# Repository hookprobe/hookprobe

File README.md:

<h1 align="center">One Node's Detection → Everyone's Protection</h1>

<p align="center">
  <strong>One security operating system. One shared evidence model. Multiple operator workspaces.</strong>
</p>

<p align="center">
  Current release: <a href="docs/releases/v0.0-26.md"><strong>HookProbe OS v0.0-26 "Zamolxis"</strong></a> (pre-release)
</p>

<p align="center">

</p>

<p align="center">
  <a href="#what-hookprobe-can-do">What it can do</a> ·
  <a href="#system-architecture">Architecture</a> ·
  <a href="#try-hookprobe">Try HookProbe</a> ·
  <a href="#hardware-roadmap-the-hookprobe-board">Hardware roadmap</a> ·
  <a href="CONTRIBUTING.md">Contribute</a>
</p>

---

## What HookProbe can do

HookProbe OS is designed to put practical security within reach: a local-first security operating
system that can observe a network, identify suspicious activity, connect detections to evidence,
and give an operator one place to understand and control what happens next.

**The operating system is HookProbe OS. SOC is its default workspace. Hardware only unlocks capabilities.**

### Manage it one way, from any client

Every management client talks to the device through **one management interface** (the management
ABI), and one component inside the kernel, **`cfgd`**, is the only thing that writes configuration.

```text
   hsh (native shell, EL0)     Mission Control (web UI)     AI copilot (tools)
              └──────────────────────┼──────────────────────┘
                          management ABI
                                     │
                     cfgd — the single configuration writer
            authenticate · authorize · validate · stage · trial · commit / revert
```

- **`hsh`** is HookProbe's own management shell, built into the kernel. It is not Bash, BusyBox or a
  Linux shell. It runs as an isolated user-mode component, sees the same numbers Mission Control
  does, and cannot reach kernel internals. Its read commands pass on CM5
  ([batch 59–63](docs/design/metal-evidence/20261111-batch59-63.md)). Production access was decided on
  2026-11-12: a console in Mission Control over the owner's HTTPS session; every command that changes
  something needs a request signed off-device with the owner's key, so the console itself carries no
  authority. That signed path is QEMU-tested only (metal pending); no serial-console access is built.
  See the [`hsh` design](docs/design/hsh-native-management-shell.md) and the
  [signed request format](docs/design/mgmt-envelope-api.md).
- **Mission Control** is the web UI, served by the device itself. It is a client of the same
  interface, with nothing UI-specific on the device.
- **Configuration is signed, not trusted.** The owner holds a signing key (in the browser, with an
  encrypted backup) and enrolls it as the device's owner key; after that the device accepts only
  configuration signed with it. Internet, Wi-Fi and firewall settings travel as one signed bundle,
  bound to the device. A bundle starts as a **trial**: the device keeps it once the internet works,
  or goes back to the last good settings by itself (proven on CM5 after a reboot,
  [batch 59–63](docs/design/metal-evidence/20261111-batch59-63.md)). Changes to how you reach the
  device must be confirmed by the owner, with a request signed by the owner's key.
- Built on main 2026-11-12, **QEMU-tested only, not yet run on CM5**: stored configuration (including
  the Wi-Fi and PPPoE passwords) encrypted at rest with a device-bound key, and firewall, internet and
  Wi-Fi changes applied live, without a reboot, with the same trial and automatic revert
  ([design and status](docs/design/heqk-sealed-config-live-apply.md)).
- Still to come: passkey signing.

Details: [ADR 0058](docs/adr/0058-owner-signed-runtime-config.md) (owner-signed configuration),
[ADR 0059](docs/adr/0059-secure-configuration-management.md) (secure configuration management) and
the [Mission Control UI requirements](docs/design/mission-control-ui-requirements.md).

### Protect locally

Inspect and respond at the device, without making cloud connectivity, an account, or an AI service a
precondition for local protection. Detection is designed to be observable by default; enforcement
is a separate, policy-controlled decision that protects legitimate traffic and management access.

### Turn signals into an understandable story

Bring supported network and device signals into a shared evidence model. Link a detection to its
flows, affected assets, related events, and response so an operator can move from “something
happened” to “why it matters” without jumping between disconnected tools.

### Operate one system through many workspaces

Mission Control is the operator's home. Observe, Detect, Investigate, Protect, Network, Intelligence,
and other workspaces are views over shared system state—not separate products with separate data.
The same evidence can support a responder's investigation and an operator's broader view.

### Make security decisions reviewable

State an outcome instead of hand-editing a pile of device settings. AEGIS is designed to reconcile
authorized desired state deterministically; an optional AI planner can help turn intent into an
explainable plan. The kernel—not an AI model—remains responsible for enforcing authorized policy.

### Grow from one device to a fleet

Start standalone, including in disconnected environments. Add a cloud-linked or self-hosted control
plane when fleet coordination is useful. The longer-term vision is opt-in sharing of validated,
privacy-preserving threat knowledge, so one node's detection can help protect others; a live global
threat-sharing mesh is not a prerequisite for the product.

## System architecture

HookProbe connects local signals to local decisions and operator-visible evidence. Hardware
capabilities shape what a device can do; they do not turn it into a different product.

<p align="center"><em>One local system, one evidence model, many views. Fleet coordination is additive.</em></p>

| Part of the system | Responsibility |
|---|---|
| **heqk and platform capabilities** | The intended common OS substrate. A platform contributes its hardware port and the capabilities it can safely provide. |
| **Local packet and policy path** | Examines supported traffic and applies an explicit, locally enforceable verdict. It does not depend on a browser, cloud, or model response. |
| **Senzorium** | Observation and telemetry: bring supported signals into a useful, normalized form. |
| **NAPSE, QSecBit, and HYDRA** | Network threat detection, security-posture signals, and threat-intelligence enrichment. |
| **Evidence graph** | Connects assets, events, detections, incidents, and responses so each workspace can follow the same facts. |
| **AEGIS** | Reconciles authorized intent into system state; optional AI assists planning but does not enforce it. |
| **cfgd and the management ABI** | The single writer of device configuration: checks who asks and what is signed, stages a change as a trial, commits it or reverts it. Every management client goes through it. |
| **hsh** | HookProbe's own management shell inside the kernel: a small, deterministic command line over the same management ABI. |
| **Mission Control** | The on-device web experience, with workspaces for understanding and managing the system; a client of the same management ABI. |
| **Optional control plane** | Adds fleet enrollment and coordination without becoming a requirement for local operation. |

These are architectural responsibilities, not a promise that every named service is already a
separate process on every device. The [high-level design](docs/design/hookprobe-high-level-design.md)
explains the product boundaries; the [heqk low-level design](docs/design/heqk-low-level-design.md)
covers the kernel, hardware, and packet path. The current platform and milestone plan is in the
[Build Plan](docs/roadmap/BuildPlan.md).

## The mission

Security should not be a privilege reserved for organizations with large budgets. People should not
have to depend on opaque systems for their safety and data, or face shared threats in isolation.

HookProbe aims to make protection more accessible, understandable, and collaborative. The long-term
vision is that defenders can choose to share validated, privacy-preserving threat knowledge—turning
one node's detection into protection for others.

Read the [HookProbe Manifesto](legacy/v1/MANIFESTO.md) for the project's original mission and values.
Its technical descriptions refer to the earlier V1 implementation; this repository's current
architecture is documented in the designs linked above.

## Hardware roadmap: the HookProbe board

HookProbe OS runs on a Raspberry Pi Compute Module 5 today. Next, we are designing a board of our own: a
security appliance built around the RK3588, with everything a home or small-office gateway needs on one
board.

| | Raspberry Pi CM5 today | HookProbe board |
|---|---|---|
| Ethernet | 1 GbE + a carrier port | **2 × 2.5 GbE** |
| Device identity | Derived from one-time-programmable fuses | **TPM 2.0 key store** |
| Wi-Fi | Wi-Fi 5, on-module | **Wi-Fi 7 (Qualcomm QCN9274), M.2** |
| Backup internet | — | **5G modem (Sierra Wireless EM9293) + nano-SIM** |
| Local retention | eMMC | **eMMC + NVMe SSD** |
| On-device AI | — | **RK3588 NPU (6 TOPS) + an M.2 slot for an AI accelerator card** |

**Room for AI.** Besides the NPU built into the RK3588, the board has a dedicated **M.2 M-key 2280 slot for an AI
accelerator card** (an NPU card, or an FPGA). Detection and classification models can run on the box with no cloud
call, and the card can be upgraded as accelerators improve. In rev A the slot has one PCIe 3.0 lane and
about 10 W of power. Which cards HookProbe OS supports will be decided on the prototype.

The software doesn't fork for it. The board is one hardware profile, and each part unlocks its
feature in Mission Control once it is proven on real hardware.

**The path.** Each step is a pass/fail test on real hardware:

| Gate | What has to be true | Status |
|---|---|---|
| **H0** | HookProbe OS validated on CM5: long-run soak, thermal and scale tests, independent security sign-off, hardware test gate green | **in progress** |
| **H1** | The kernel's hardware layer separated, so a new board is a profile, not a fork | planned |
| **H2** | HookProbe OS proven on an off-the-shelf RK3588 board, with Wi-Fi 7 and 5G brought up there first | planned |
| **H3** | Our board routed, then reviewed for signal and power integrity | planned |
| **H4** | Prototypes built and measured: both ports, NVMe, TPM, radios, thermal | planned |
| **H5** | Release: reproducible board image, manufacturing package, certified units | planned |

**Where it stands (November 2026).** Rev A schematic and component placement are complete, pass
90 automated design checks, and are [public in this repository](hardware/hookprobe-sbc/). The board is not routed yet and has not been built; there is nothing to
buy. Performance figures will come from prototype measurements.

**Reference material.**
- [ADR 0064: HookProbe hardware program](docs/adr/0064-hookprobe-hardware-program.md): the gates, the driver
  work, the boot chain and root of trust, and the licence.
- [`appliance/hookprobe-sbc/`](appliance/hookprobe-sbc/): how HookProbe OS sees the board and what each part
  unlocks.
- [Build Plan, Track H](docs/roadmap/BuildPlan.md): live status.
- **The design itself: [`hardware/hookprobe-sbc/`](hardware/hookprobe-sbc/)**: schematic (PDF and KiCad), component
  placement, BOM, 3D model, the generator scripts and the validation report. Published as work in progress under
  **CERN-OHL-S-2.0**, with a commercial licence for closed derivatives
  ([`hardware/README.md`](hardware/README.md)). Review it and tell us what you find.

**Help us build it.** We are looking for:
- **Hardware engineers** with RK3588 / LPDDR4X layout experience for routing and signal- and power-integrity
  review (H3), and for prototype bring-up (H4).
- **Kernel and driver developers** for the RK3588 port: PCIe, RTL8125, NVMe, TPM, Qualcomm Wi-Fi 7, 5G (H1–H2),
  and the RK3588 NPU and M.2 AI accelerator cards.
- **Sponsors and funders** for prototype runs, compliance testing and the first production batch.

Sponsor through [GitHub Sponsors](https://github.com/sponsors/hookprobe) or
[Open Collective](https://opencollective.com/hookprobe). To work on the board, fund it or partner with us,
start a thread in [GitHub Discussions](https://github.com/hookprobe/hookprobe/discussions) or email
**qsecbit@hookprobe.com**.

## Try HookProbe

### Explore the dashboard demo

[Open the hosted demo](https://mssp.hookprobe.com/?site=demo-site). It uses simulated data to
illustrate the fleet dashboard; it is not a live security sensor or the on-device operating system.

### Build and explore in QEMU

For the developer environment and prerequisites, see the [heqk setup guide](os/kernel/HACKING.md).
Then run:

```sh
os/kernel/validate.sh
os/kernel/tools/mc-e2e.sh
```

The first command validates implemented kernel phases under QEMU. The second exercises a browser
flow from a test attack through heqk detection to evidence in Mission Control.

To check the Mission Control UI on its own (typecheck plus the behaviour suite, no QEMU needed), or
everything CI runs for it:

```sh
os/mission-control/tests/ui/run.sh
tools/ci/gates.sh g3
```

### Explore the design

- [HookProbe high-level design](docs/design/hookprobe-high-level-design.md)
- [heqk low-level design](docs/design/heqk-low-level-design.md)
- [OS architecture](docs/architecture/Readme.md)
- [Mission Control specification](docs/architecture/MissionControl.md)
- [Mission Control UI layouts and requirements](docs/design/mission-control-ui-requirements.md) (incl. the configuration journey)
- [ADR 0058 — owner-signed configuration on a running device](docs/adr/0058-owner-signed-runtime-config.md)
- [ADR 0059 — secure configuration management (cfgd, signed bundles, trial and revert)](docs/adr/0059-secure-configuration-management.md)
- [`hsh` — the native management shell](docs/design/hsh-native-management-shell.md)
- [CM5 bench acceptance record](docs/design/bench-runbook-prod-mc-2026-11.md)
- [ADR 0064 — HookProbe hardware program (the RK3588 board)](docs/adr/0064-hookprobe-hardware-program.md)
- [Current roadmap and engineering gaps](docs/roadmap/BuildPlan.md)

## Contribute

Code, testing, documentation, and carefully investigated issue reports are welcome.

- Read the [contributing guide](CONTRIBUTING.md).
- Browse [open issues](https://github.com/hookprobe/hookprobe/issues).
- Join [GitHub Discussions](https://github.com/hookprobe/hookprobe/discussions).

Please report vulnerabilities privately using the [security policy](SECURITY.md), not in a public
issue.

## Project growth

Repository stars over time:

<p align="center">
  <a href="https://star-history.com/#hookprobe/hookprobe&Date">
    <picture>
      <source media="(prefers-color-scheme: dark)" srcset="https://api.star-history.com/svg?repos=hookprobe/hookprobe&type=Date&theme=dark" />
      <source media="(prefers-color-scheme: light)" srcset="https://api.star-history.com/svg?repos=hookprobe/hookprobe&type=Date" />
      
    </picture>
  </a>
</p>

## License

All HookProbe software is licensed under **AGPL-3.0-only**, and the hardware designs in
[`hardware/`](hardware/) under **CERN-OHL-S-2.0**; both are also available under a commercial licence.
Third-party components keep their own licences. See [LICENSING.md](LICENSING.md) and [LICENSE](LICENSE).
The original HookProbe V1 implementation is preserved in [`legacy/v1/`](legacy/v1/).

<p align="center">
  <strong>HookProbe OS</strong><br/>
  Local protection. Shared intelligence. Evidence-driven security.<br/>
  <a href="https://hookprobe.com/">hookprobe.com</a> ·
  <a href="https://github.com/sponsors/hookprobe">Sponsor development</a>
</p>

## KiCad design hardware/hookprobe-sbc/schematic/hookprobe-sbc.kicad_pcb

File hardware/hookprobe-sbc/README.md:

# HookProbe SBC (rev A, design in progress)

A single-board computer for HookProbe, designed chip-down around the Rockchip RK3588.
The schematic and the component placement are generated by Python scripts and checked by an
end-to-end validation script.

**Status: schematic and placement complete and validated. The board is NOT routed and has not been
built. Do not order it from these files.** See "What is not done" below.

> **Place in HookProbe OS.** This is the design for HookProbe's own hardware, published as work in progress.
> Direction, gates and the heqk port plan are in [ADR 0064](../../docs/adr/0064-hookprobe-hardware-program.md):
> CM5 is validated first (H0), and heqk is proven on an off-the-shelf RK3588 board before this one (H2 → H4).
> How the OS sees the board: [`appliance/hookprobe-sbc/`](../../appliance/hookprobe-sbc/).
> **Licence:** CERN-OHL-S-2.0, or a commercial licence from HookProbe ([`../README.md`](../README.md)).
> **Feedback is welcome**: open an issue or a Discussion with what you found, and the sheet or reference.

## What is on the board

| Function | Implementation |
|---|---|
| Processor | Rockchip RK3588 (8 cores, built-in NPU) |
| Memory | 2 x LPDDR4X (200-ball) |
| Storage | eMMC (153-ball) soldered, M.2 M-key slot for an NVMe SSD (2280) |
| Ethernet | 2 x 2.5 Gb, RTL8125BG, each on its own PCIe lane |
| Wi-Fi | M.2 E-key slot (2230) for a tri-band card |
| 5G | M.2 B-key slot (3052) on USB 3, nano-SIM holder |
| Thread / Matter | ESP32-H2-MINI-1 module |
| AI accelerator | M.2 M-key slot (2280) for an AI accelerator (NPU) or FPGA card, PCIe 3.0 ×1, ~10 W budget |
| USB | 2 x USB-C (USB 3, DisplayPort, power delivery), 2 x USB-A (USB 2.0, stacked) |
| Security | TPM 2.0 (SLB 9670), reset tied to the platform reset |
| Other | RTC with battery connector, fan header, debug serial port, power / reset header |
| Power | 12 V to 20 V on a DC jack, or USB-C port 1 (5 V at start, 20 V after negotiation) |
| Size | 140 x 128 mm, 8 layers, M3 mounting holes in the corners |

All external ports are on one edge. The processor and both memory chips sit under one 40 x 40 mm
heatsink with a fan (hole pattern of the Radxa Heatsink 4012). The four M.2 cards are on the underside,
facing the case base, so thermal pads can carry their heat into the case.

## Files

| Path | Contents |
|---|---|
| `docs/hookprobe-sbc-schematic.pdf` | Schematic, 25 sheets |
| `docs/hookprobe-sbc-placement-top.pdf`, `-bottom.pdf` | Component placement drawings |
| `docs/hookprobe-sbc-bom.csv` | Parts list, grouped by value (LCSC numbers where chosen) |
| `docs/images/` | Placement images and 3D views |
| `docs/3d/hookprobe-sbc.step` | 3D model of the board (many vendor parts have no 3D body yet) |
| `schematic/` | KiCad project: schematic sheets, board file, project-local symbol and footprint library |
| `schematic/build.py` | Generates the schematic (every part and connection is defined here) |
| `schematic/build_pcb.py` | Generates the board file: outline, holes, component placement |
| `design/power_check.py` | Power-tree check: regulator voltages, pin limits, power-up order, loads |
| `design/allocation_check.py` | High-speed interface allocation and load budget |
| `tools/board_rules.py` | Writes JLCPCB's manufacturing limits and the net classes into the project |
| `validate.py` | End-to-end validation; writes `VALIDATION.md` |
| `VALIDATION.md` | Latest validation report |

## Regenerating and checking

Needs KiCad (the scripts call `kicad-cli`) and Python 3. The files are written in the format of a KiCad 10.99
nightly build. On Linux the scripts find `kicad-cli` on `PATH` and the stock libraries under `/usr/share/kicad`;
override with `KICAD_CLI`, `KICAD_SYMBOL_DIR` and `KICAD_FOOTPRINT_DIR`. `design/allocation_check.py` needs only
Python. Vendor datasheets (`vendor/*/datasheet.pdf`) are not in the repository; download them from LCSC.

```bash
python3 schematic/build.py          # schematic
python3 schematic/build_pcb.py      # board file with placement
python3 tools/board_rules.py        # manufacturing limits and net classes
python3 validate.py                 # full check, about ten minutes
```

The latest run passed 90 of 90 checks: the KiCad netlist matches the intended connections, the
electrical rules check is clean, every schematic pin reaches the right pad on the board, the board
check shows no errors under JLCPCB's published limits, and the power tree is within every chip's
datasheet limits.

## What is not done

- **Routing.** No tracks, no planes. This is the largest remaining task and needs a layout engineer
  with RK3588 / LPDDR4X experience, followed by signal- and power-integrity review.
- **Stack-up and impedance.** Track widths for PCIe, USB and Ethernet pairs are computed starting
  values, to be replaced with the manufacturer's figures.
- **Parts still to confirm:** a 2.5 Gb-rated Ethernet jack (the placed one is rated 1 Gb), the
  ideal-diode transistors, the ESD substitutes, the enable-clamp zener.
- **Assumptions still to confirm:** PCIe lane mapping, M.2 socket orientation, Thread antenna
  direction, memory placement against Rockchip's layout template.
- **Input over-voltage:** the input converters' absolute maximum is 26 V. Use 20 V or less.
- **USB-C power** depends on the bootloader negotiating 20 V, as on the Radxa ROCK 5B.
- Silkscreen clean-up, test points, assembly files, prototype bring-up, compliance testing.

An independent review by a design house or by Rockchip's field engineers is strongly recommended
before any money is spent on manufacturing.

## Reference design

Large parts of the processor, memory and power circuits follow the published Radxa ROCK 5B v1.45
schematic. The reference schematic and the component datasheets are not included in this repository;
download them from their owners.

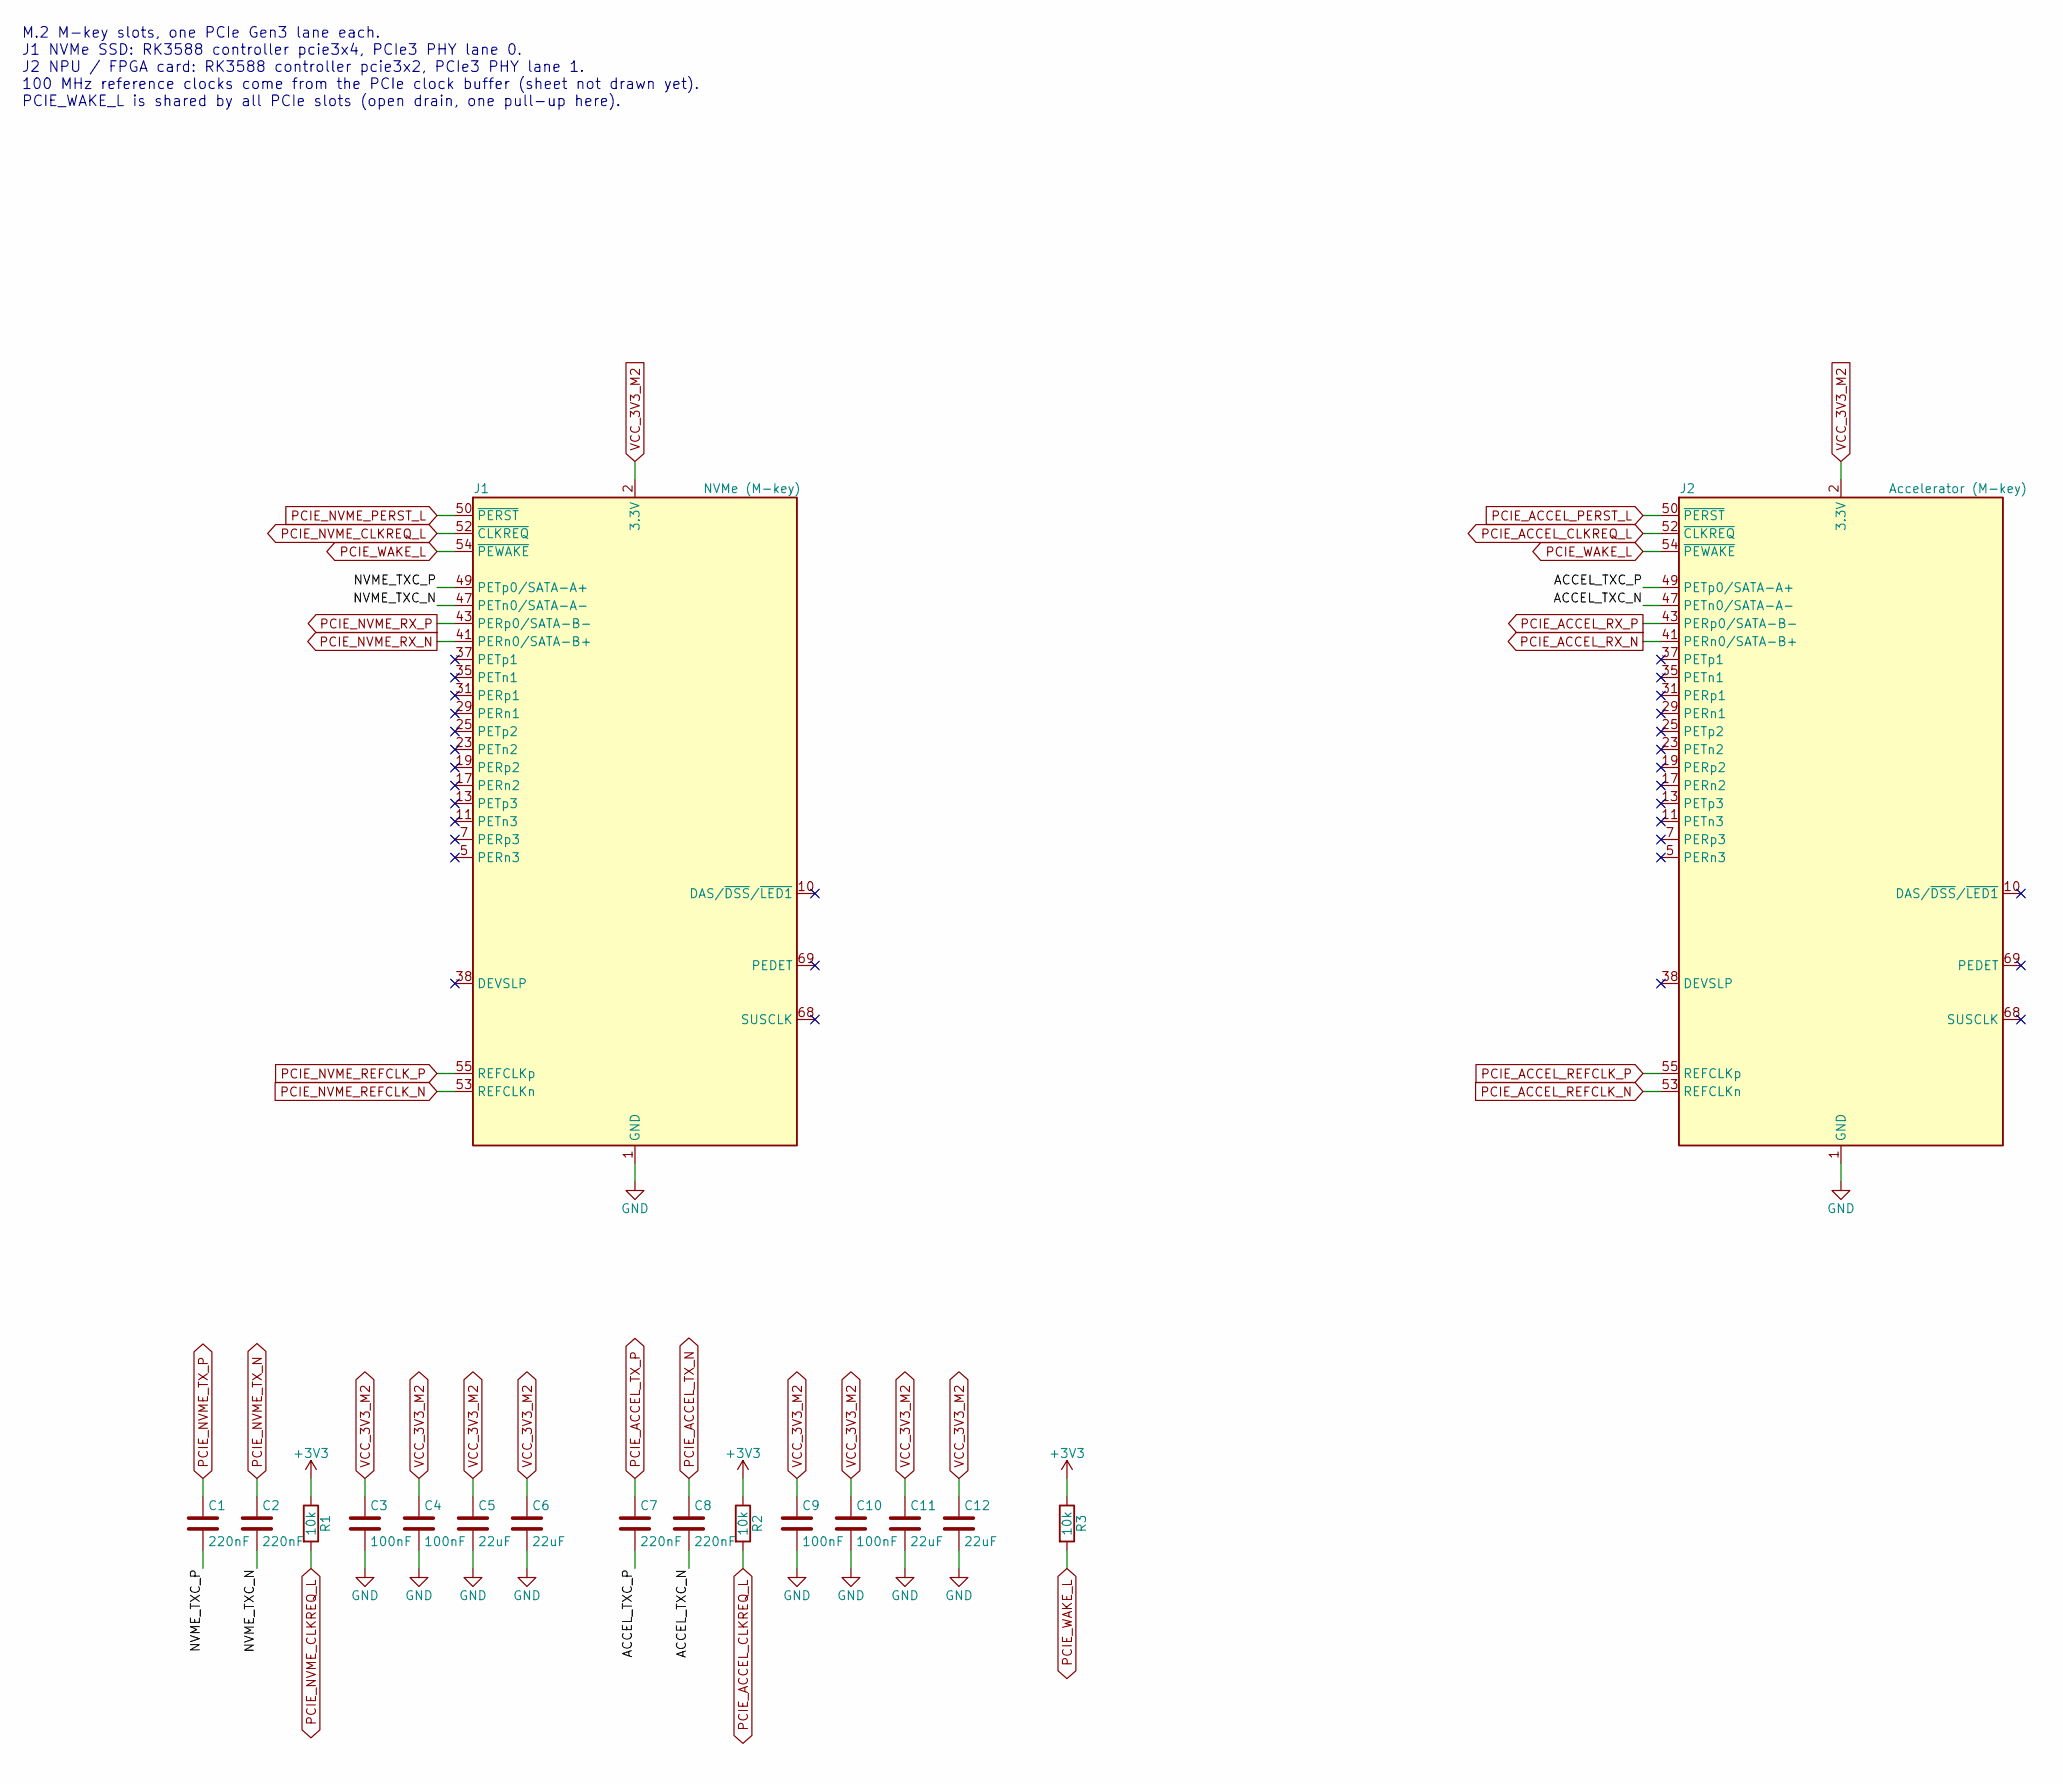
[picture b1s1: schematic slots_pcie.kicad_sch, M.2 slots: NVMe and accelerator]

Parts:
C1, C2, C7, C8: 220nF; C_0402_1005Metric
C3, C4, C9, C10: 100nF; C_0402_1005Metric
C5, C6, C11, C12: 22uF; C_0805_2012Metric
J1: NVMe (M-key); PCIE-SMD_75P-P0.50_1-2199230-5; Part TE 1-2199230-5, M.2 M-key socket, 4.2 mm; LCSC C590854
J2: Accelerator (M-key); PCIE-SMD_75P-P0.50_1-2199230-5; Part TE 1-2199230-5, M.2 M-key socket, 4.2 mm; LCSC C590854
R1, R2, R3: 10k; R_0402_1005Metric

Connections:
+3V3: R1.1, R2.1, R3.1; also elsewhere on the board
/M.2 slots: NVMe and accelerator/ACCEL_TXC_N: C8.2, J2.47 (PETn0/SATA-A-)
/M.2 slots: NVMe and accelerator/ACCEL_TXC_P: C7.2, J2.49 (PETp0/SATA-A+)
/M.2 slots: NVMe and accelerator/NVME_TXC_N: C2.2, J1.47 (PETn0/SATA-A-)
/M.2 slots: NVMe and accelerator/NVME_TXC_P: C1.2, J1.49 (PETp0/SATA-A+)
GND: C3.2, C4.2, C5.2, C6.2, C9.2, C10.2, C11.2, C12.2, J1.1 (GND), J1.3 (GND), J1.9 (GND), J1.15 (GND), J1.21 (GND), J1.27 (GND), J1.33 (GND), J1.39 (GND), J1.45 (GND), J1.51 (GND), J1.57 (GND), J1.71 (GND), J1.73 (GND), J1.75 (GND), J2.1 (GND), J2.3 (GND), J2.9 (GND), J2.15 (GND), J2.21 (GND), J2.27 (GND), J2.33 (GND), J2.39 (GND), J2.45 (GND), J2.51 (GND), J2.57 (GND), J2.71 (GND), J2.73 (GND), J2.75 (GND); also elsewhere on the board
PCIE_ACCEL_CLKREQ_L: J2.52 (~CLKREQ), R2.2; also elsewhere on the board
PCIE_ACCEL_PERST_L: J2.50 (~PERST); also elsewhere on the board
PCIE_ACCEL_REFCLK_N: J2.53 (REFCLKn); also elsewhere on the board
PCIE_ACCEL_REFCLK_P: J2.55 (REFCLKp); also elsewhere on the board
PCIE_ACCEL_RX_N: J2.41 (PERn0/SATA-B+); also elsewhere on the board
PCIE_ACCEL_RX_P: J2.43 (PERp0/SATA-B-); also elsewhere on the board
PCIE_ACCEL_TX_N: C8.1; also elsewhere on the board
PCIE_ACCEL_TX_P: C7.1; also elsewhere on the board
PCIE_NVME_CLKREQ_L: J1.52 (~CLKREQ), R1.2; also elsewhere on the board
PCIE_NVME_PERST_L: J1.50 (~PERST); also elsewhere on the board
PCIE_NVME_REFCLK_N: J1.53 (REFCLKn); also elsewhere on the board
PCIE_NVME_REFCLK_P: J1.55 (REFCLKp); also elsewhere on the board
PCIE_NVME_RX_N: J1.41 (PERn0/SATA-B+); also elsewhere on the board
PCIE_NVME_RX_P: J1.43 (PERp0/SATA-B-); also elsewhere on the board
PCIE_NVME_TX_N: C2.1; also elsewhere on the board
PCIE_NVME_TX_P: C1.1; also elsewhere on the board
PCIE_WAKE_L: J1.54 (~PEWAKE), J2.54 (~PEWAKE), R3.2; also elsewhere on the board
VCC_3V3_M2: C3.1, C4.1, C5.1, C6.1, C9.1, C10.1, C11.1, C12.1, J1.2 (3.3V), J1.4 (3.3V), J1.12 (3.3V), J1.14 (3.3V), J1.16 (3.3V), J1.18 (3.3V), J1.70 (3.3V), J1.72 (3.3V), J1.74 (3.3V), J2.2 (3.3V), J2.4 (3.3V), J2.12 (3.3V), J2.14 (3.3V), J2.16 (3.3V), J2.18 (3.3V), J2.70 (3.3V), J2.72 (3.3V), J2.74 (3.3V); also elsewhere on the board

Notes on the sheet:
M.2 M-key slots, one PCIe Gen3 lane each. J1 NVMe SSD: RK3588 controller pcie3x4, PCIe3 PHY lane 0. J2 NPU / FPGA card: RK3588 controller pcie3x2, PCIe3 PHY lane 1. 100 MHz reference clocks come from the PCIe clock buffer (sheet not drawn yet). PCIE_WAKE_L is shared by all PCIe slots (open drain, o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

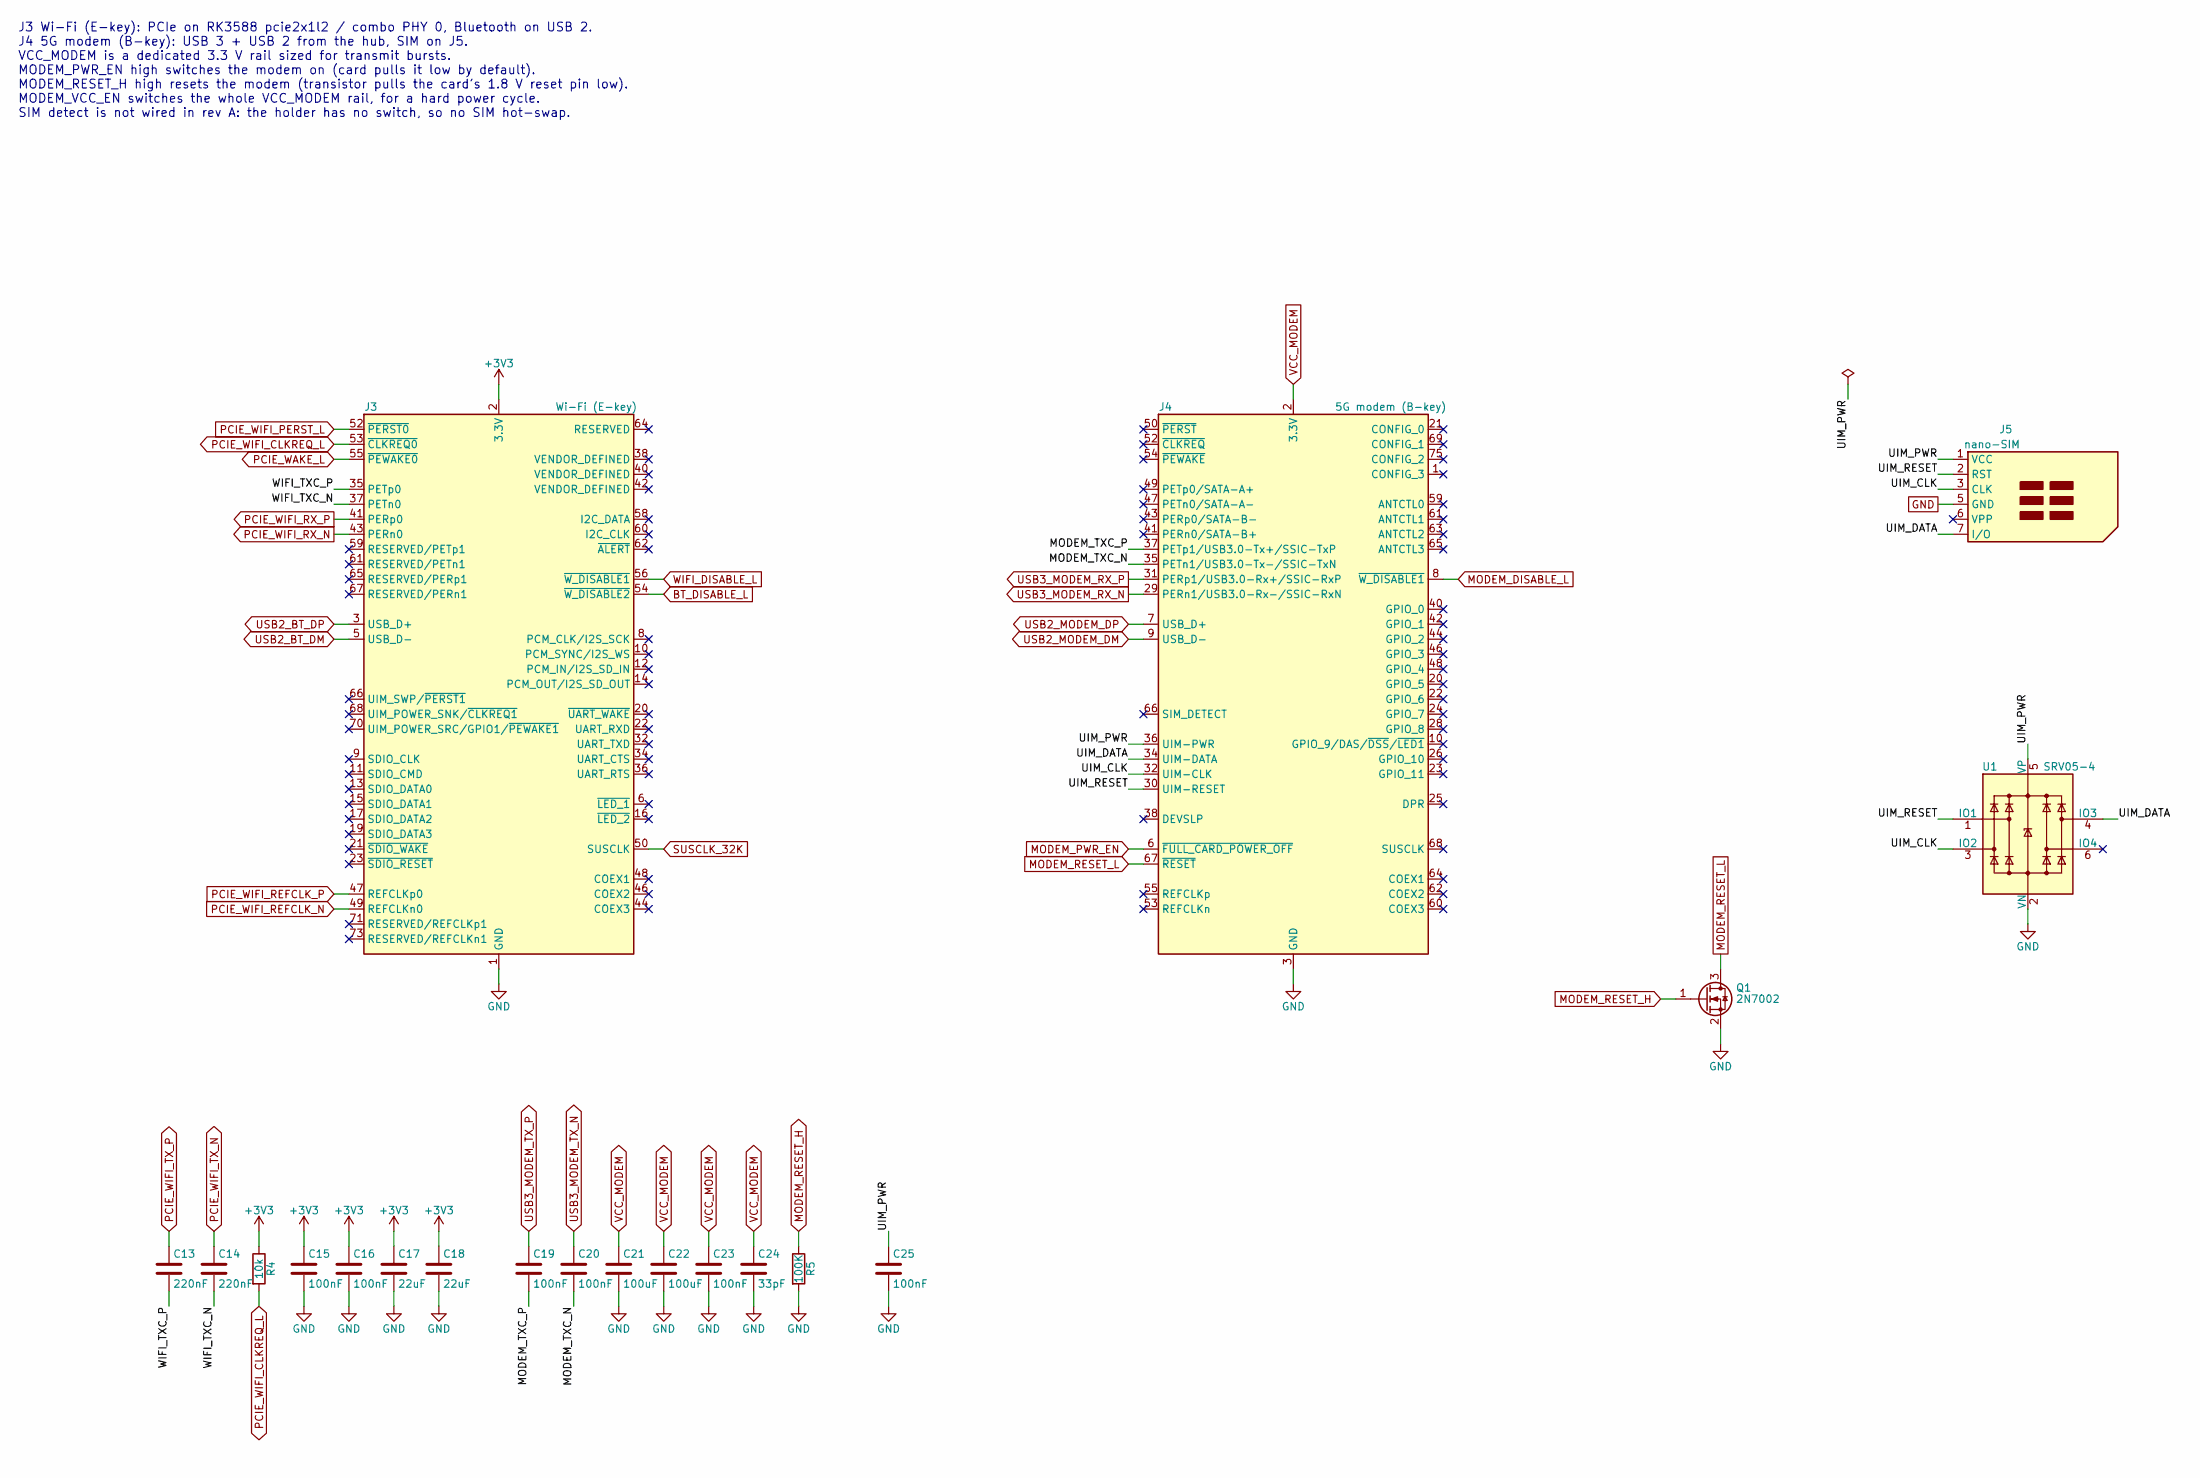
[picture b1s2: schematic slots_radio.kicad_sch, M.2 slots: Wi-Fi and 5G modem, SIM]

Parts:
C13, C14: 220nF; C_0402_1005Metric
C15, C16, C19, C20, C23, C25: 100nF; C_0402_1005Metric
C17, C18: 22uF; C_0805_2012Metric
C21, C22: 100uF; C_1210_3225Metric
C24: 33pF; C_0402_1005Metric
J3: Wi-Fi (E-key); CONN-SMD_67P-P0.50-V_NXSE0-S67XX-XXH4; Part Argosy NASE0-S6701-TSH4, M.2 E-key sock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; LCSC C367027
J4: 5G modem (B-key); PCIE-SMD_2199230-3_1; Part TE 2199230-3, M.2 B-key socket, 4.2 mm; LCSC C590859
J5: nano-SIM; nanoSIM_GCT_SIM8060-6-0-14-00
Q1: 2N7002; SOT-23
R4: 10k; R_0402_1005Metric
R5: 100K; R_0402_1005Metric
U1: SRV05-4; SOT-23-6

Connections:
+3V3: C15.1, C16.1, C17.1, C18.1, J3.2 (3.3V), J3.4 (3.3V), J3.72 (3.3V), J3.74 (3.3V), R4.1; also elsewhere on the board
/M.2 slots: Wi-Fi and 5G modem, SIM/MODEM_TXC_N: C20.2, J4.35 (PETn1/USB3.0-Tx-/SSIC-TxN)
/M.2 slots: Wi-Fi and 5G modem, SIM/MODEM_TXC_P: C19.2, J4.37 (PETp1/USB3.0-Tx+/SSIC-TxP)
/M.2 slots: Wi-Fi and 5G modem, SIM/UIM_CLK: J4.32 (UIM-CLK), J5.3 (CLK), U1.3 (IO2)
/M.2 slots: Wi-Fi and 5G modem, SIM/UIM_DATA: J4.34 (UIM-DATA), J5.7 (I/O), U1.4 (IO3)
/M.2 slots: Wi-Fi and 5G modem, SIM/UIM_PWR: C25.1, J4.36 (UIM-PWR), J5.1 (VCC), U1.5 (VP)
/M.2 slots: Wi-Fi and 5G modem, SIM/UIM_RESET: J4.30 (UIM-RESET), J5.2 (RST), U1.1 (IO1)
/M.2 slots: Wi-Fi and 5G modem, SIM/WIFI_TXC_N: C14.2, J3.37 (PETn0)
/M.2 slots: Wi-Fi and 5G modem, SIM/WIFI_TXC_P: C13.2, J3.35 (PETp0)
BT_DISABLE_L: J3.54 (~W_DISABLE2); also elsewhere on the board
GND: C15.2, C16.2, C17.2, C18.2, C21.2, C22.2, C23.2, C24.2, C25.2, J3.1 (GND), J3.7 (GND), J3.18 (GND), J3.33 (GND), J3.39 (GND), J3.45 (GND), J3.51 (GND), J3.57 (GND), J3.63 (GND), J3.69 (GND), J3.75 (GND), J4.3 (GND), J4.5 (GND), J4.11 (GND), J4.27 (GND), J4.33 (GND), J4.39 (GND), J4.45 (GND), J4.51 (GND), J4.57 (GND), J4.71 (GND), J4.73 (GND), J5.5 (GND), Q1.2 (S), R5.2, U1.2 (VN); also elsewhere on the board
MODEM_DISABLE_L: J4.8 (~W_DISABLE1); also elsewhere on the board
MODEM_PWR_EN: J4.6 (~FULL_CARD_POWER_OFF); also elsewhere on the board
MODEM_RESET_H: Q1.1 (G), R5.1; also elsewhere on the board
MODEM_RESET_L: J4.67 (~RESET), Q1.3 (D)
PCIE_WAKE_L: J3.55 (~PEWAKE0); also elsewhere on the board
PCIE_WIFI_CLKREQ_L: J3.53 (~CLKREQ0), R4.2; also elsewhere on the board
PCIE_WIFI_PERST_L: J3.52 (~PERST0); also elsewhere on the board
PCIE_WIFI_REFCLK_N: J3.49 (REFCLKn0); also elsewhere on the board
PCIE_WIFI_REFCLK_P: J3.47 (REFCLKp0); also elsewhere on the board
PCIE_WIFI_RX_N: J3.43 (PERn0); also elsewhere on the board
PCIE_WIFI_RX_P: J3.41 (PERp0); also elsewhere on the board
PCIE_WIFI_TX_N: C14.1; also elsewhere on the board
PCIE_WIFI_TX_P: C13.1; also elsewhere on the board
SUSCLK_32K: J3.50 (SUSCLK); also elsewhere on the board
USB2_BT_DM: J3.5 (USB_D-); also elsewhere on the board
USB2_BT_DP: J3.3 (USB_D+); also elsewhere on the board
USB2_MODEM_DM: J4.9 (USB_D-); also elsewhere on the board
USB2_MODEM_DP: J4.7 (USB_D+); also elsewhere on the board
USB3_MODEM_RX_N: J4.29 (PERn1/USB3.0-Rx-/SSIC-RxN); also elsewhere on the board
USB3_MODEM_RX_P: J4.31 (PERp1/USB3.0-Rx+/SSIC-RxP); also elsewhere on the board
USB3_MODEM_TX_N: C20.1; also elsewhere on the board
USB3_MODEM_TX_P: C19.1; also elsewhere on the board
VCC_MODEM: C21.1, C22.1, C23.1, C24.1, J4.2 (3.3V), J4.4 (3.3V), J4.70 (3.3V), J4.72 (3.3V), J4.74 (3.3V); also elsewhere on the board
WIFI_DISABLE_L: J3.56 (~W_DISABLE1); also elsewhere on the board

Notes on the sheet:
J3 Wi-Fi (E-key): PCIe on RK3588 pcie2x1l2 / combo PHY 0, Bluetooth on USB 2. J4 5G modem (B-key): USB 3 + USB 2 from the hub, SIM on J5. VCC_MODEM is a dedicated 3.3 V rail sized for transmit bursts. MODEM_PWR_EN high switches the modem on (card pulls it low by default). MODEM_RESET_H high resets 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

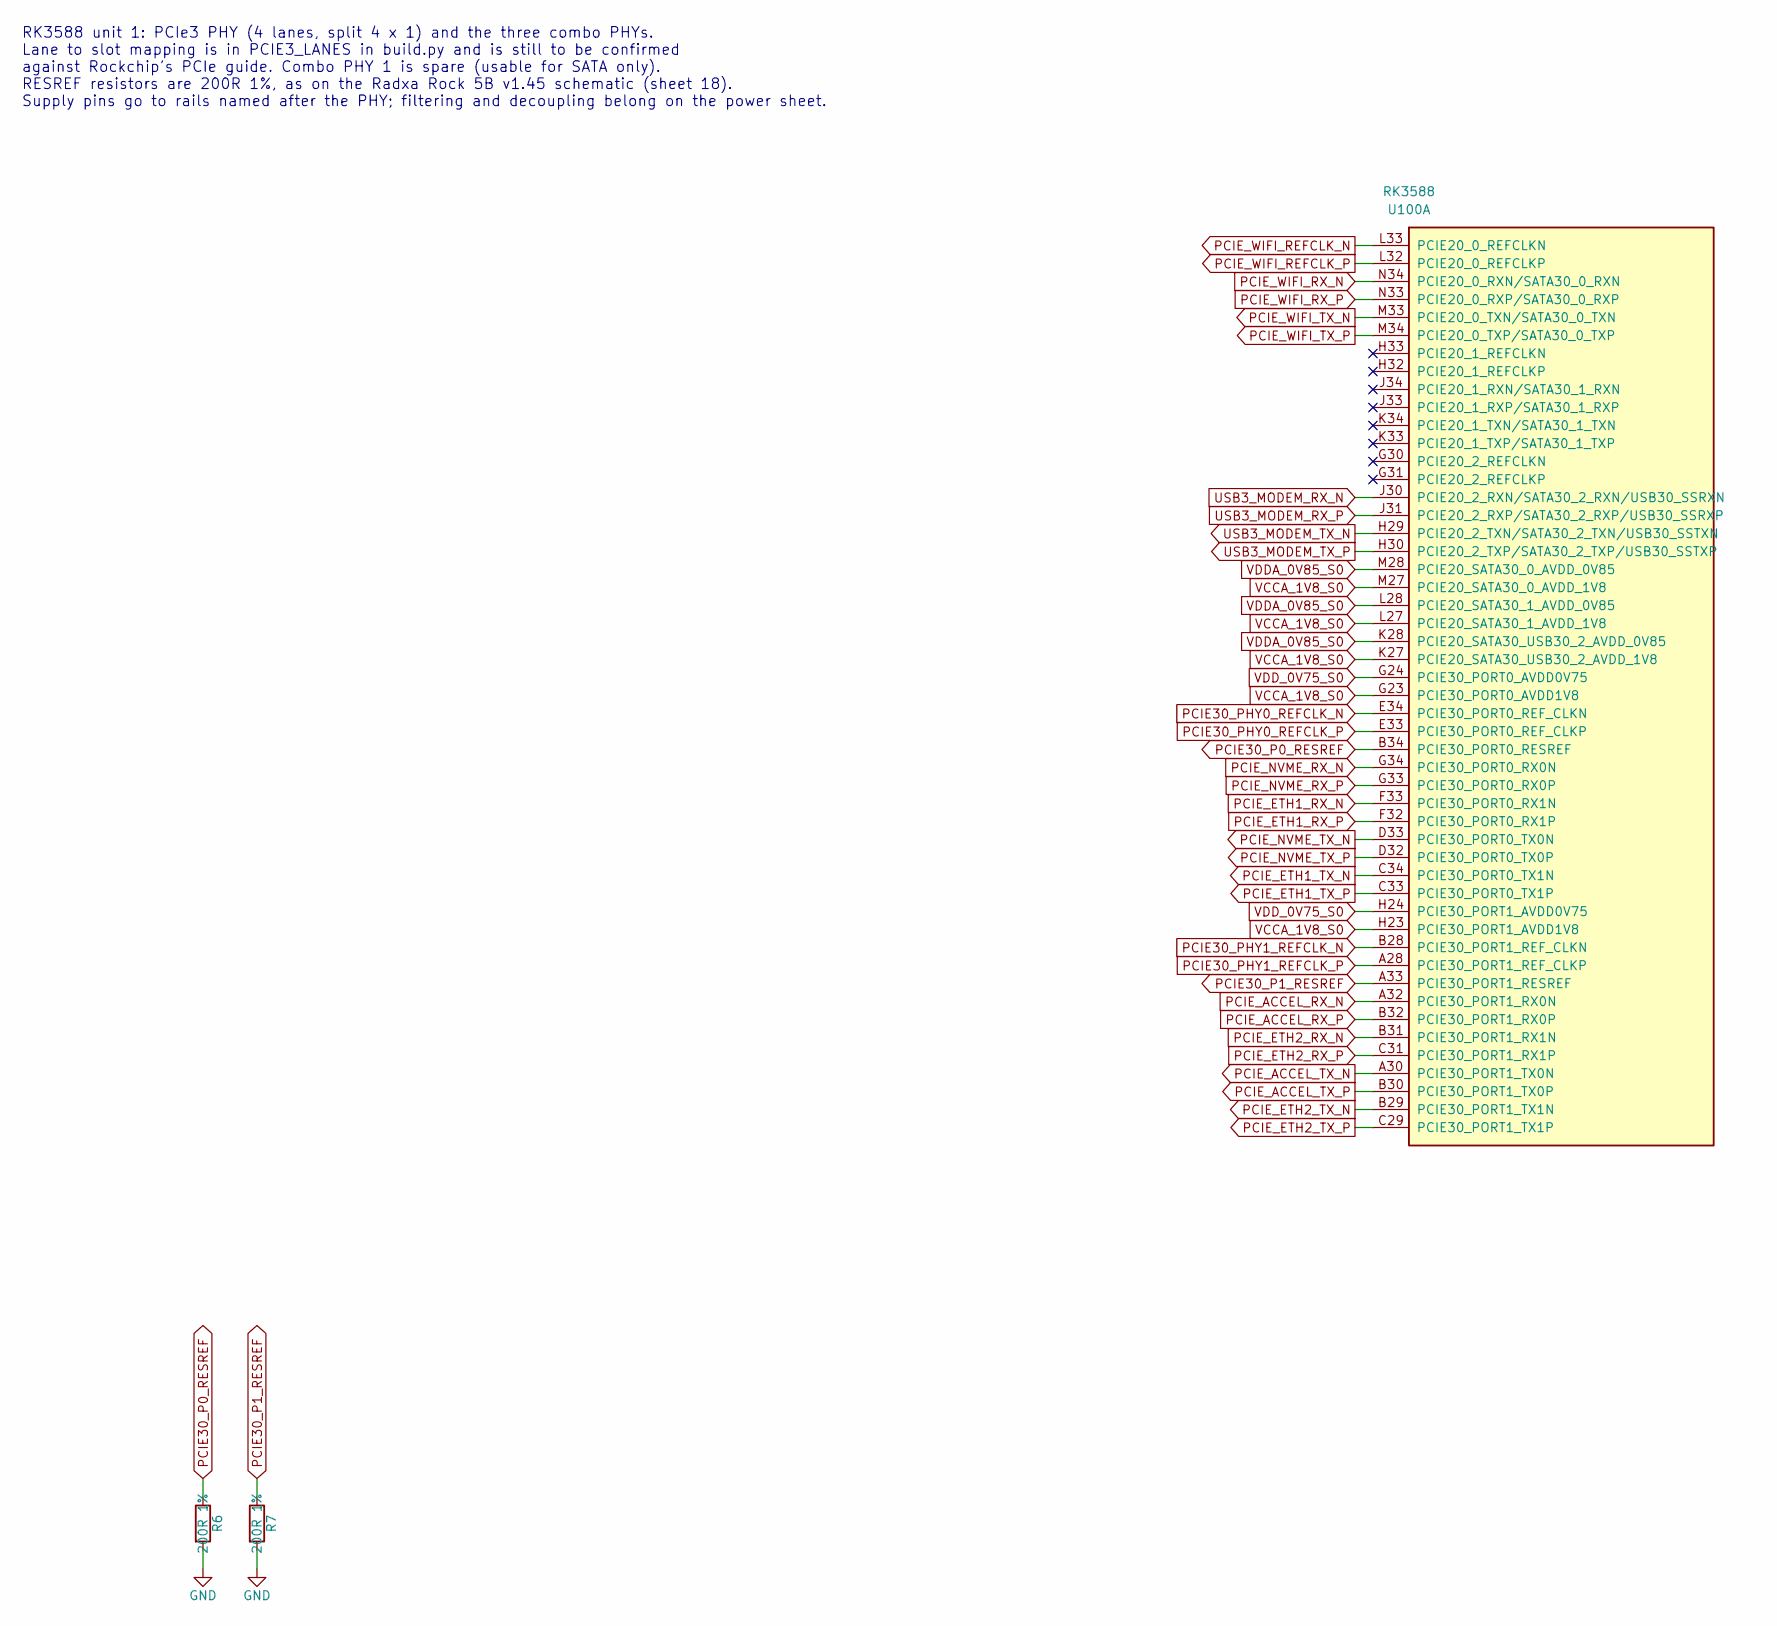
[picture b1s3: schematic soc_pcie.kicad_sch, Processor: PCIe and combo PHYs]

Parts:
R6, R7: 200R 1%; R_0402_1005Metric
U100: RK3588; FCBGA-1088_L23.0-W23.0-P0.65-TL_RK3588

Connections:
GND: R6.2, R7.2; also elsewhere on the board
PCIE30_P0_RESREF: R6.1, U100.B34 (PCIE30_PORT0_RESREF)
PCIE30_P1_RESREF: R7.1, U100.A33 (PCIE30_PORT1_RESREF)
PCIE30_PHY0_REFCLK_N: U100.E34 (PCIE30_PORT0_REF_CLKN); also elsewhere on the board
PCIE30_PHY0_REFCLK_P: U100.E33 (PCIE30_PORT0_REF_CLKP); also elsewhere on the board
PCIE30_PHY1_REFCLK_N: U100.B28 (PCIE30_PORT1_REF_CLKN); also elsewhere on the board
PCIE30_PHY1_REFCLK_P: U100.A28 (PCIE30_PORT1_REF_CLKP); also elsewhere on the board
PCIE_ACCEL_RX_N: U100.A32 (PCIE30_PORT1_RX0N); also elsewhere on the board
PCIE_ACCEL_RX_P: U100.B32 (PCIE30_PORT1_RX0P); also elsewhere on the board
PCIE_ACCEL_TX_N: U100.A30 (PCIE30_PORT1_TX0N); also elsewhere on the board
PCIE_ACCEL_TX_P: U100.B30 (PCIE30_PORT1_TX0P); also elsewhere on the board
PCIE_ETH1_RX_N: U100.F33 (PCIE30_PORT0_RX1N); also elsewhere on the board
PCIE_ETH1_RX_P: U100.F32 (PCIE30_PORT0_RX1P); also elsewhere on the board
PCIE_ETH1_TX_N: U100.C34 (PCIE30_PORT0_TX1N); also elsewhere on the board
PCIE_ETH1_TX_P: U100.C33 (PCIE30_PORT0_TX1P); also elsewhere on the board
PCIE_ETH2_RX_N: U100.B31 (PCIE30_PORT1_RX1N); also elsewhere on the board
PCIE_ETH2_RX_P: U100.C31 (PCIE30_PORT1_RX1P); also elsewhere on the board
PCIE_ETH2_TX_N: U100.B29 (PCIE30_PORT1_TX1N); also elsewhere on the board
PCIE_ETH2_TX_P: U100.C29 (PCIE30_PORT1_TX1P); also elsewhere on the board
PCIE_NVME_RX_N: U100.G34 (PCIE30_PORT0_RX0N); also elsewhere on the board
PCIE_NVME_RX_P: U100.G33 (PCIE30_PORT0_RX0P); also elsewhere on the board
PCIE_NVME_TX_N: U100.D33 (PCIE30_PORT0_TX0N); also elsewhere on the board
PCIE_NVME_TX_P: U100.D32 (PCIE30_PORT0_TX0P); also elsewhere on the board
PCIE_WIFI_REFCLK_N: U100.L33 (PCIE20_0_REFCLKN); also elsewhere on the board
PCIE_WIFI_REFCLK_P: U100.L32 (PCIE20_0_REFCLKP); also elsewhere on the board
PCIE_WIFI_RX_N: U100.N34 (PCIE20_0_RXN/SATA30_0_RXN); also elsewhere on the board
PCIE_WIFI_RX_P: U100.N33 (PCIE20_0_RXP/SATA30_0_RXP); also elsewhere on the board
PCIE_WIFI_TX_N: U100.M33 (PCIE20_0_TXN/SATA30_0_TXN); also elsewhere on the board
PCIE_WIFI_TX_P: U100.M34 (PCIE20_0_TXP/SATA30_0_TXP); also elsewhere on the board
USB3_MODEM_RX_N: U100.J30 (PCIE20_2_RXN/SATA30_2_RXN/USB30_SSRXN); also elsewhere on the board
USB3_MODEM_RX_P: U100.J31 (PCIE20_2_RXP/SATA30_2_RXP/USB30_SSRXP); also elsewhere on the board
USB3_MODEM_TX_N: U100.H29 (PCIE20_2_TXN/SATA30_2_TXN/USB30_SSTXN); also elsewhere on the board
USB3_MODEM_TX_P: U100.H30 (PCIE20_2_TXP/SATA30_2_TXP/USB30_SSTXP); also elsewhere on the board
VCCA_1V8_S0: U100.G23 (PCIE30_PORT0_AVDD1V8), U100.H23 (PCIE30_PORT1_AVDD1V8), U100.K27 (PCIE20_SATA30_USB30_2_AVDD_1V8), U100.L27 (PCIE20_SATA30_1_AVDD_1V8), U100.M27 (PCIE20_SATA30_0_AVDD_1V8); also elsewhere on the board
VDDA_0V85_S0: U100.K28 (PCIE20_SATA30_USB30_2_AVDD_0V85), U100.L28 (PCIE20_SATA30_1_AVDD_0V85), U100.M28 (PCIE20_SATA30_0_AVDD_0V85); also elsewhere on the board
VDD_0V75_S0: U100.G24 (PCIE30_PORT0_AVDD0V75), U100.H24 (PCIE30_PORT1_AVDD0V75); also elsewhere on the board

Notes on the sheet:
RK3588 unit 1: PCIe3 PHY (4 lanes, split 4 x 1) and the three combo PHYs. Lane to slot mapping is in PCIE3_LANES in build.py and is still to be confirmed against Rockchip's PCIe guide. Combo PHY 1 is spare (usable for SATA only). RESREF resistors are 200R 1%, as on the Radxa Rock 5B v1.45 schematic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

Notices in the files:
README.md:
AGPL-3.0 license
